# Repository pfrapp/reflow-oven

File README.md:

# reflow-oven
DIY reflow oven for SMD soldering

## Scope

In this project, we build an oven for reflow soldering of SMD (surface mount device)
parts, such as for instance microcontrollers etc.
In general, it will help to move away from THT (through hole technology)
boards and enter the realm of SMT (surface mount technology) boards.
This saves space, helps to get rid of evaluation-board-style setups,
and enables fully embedded circuits.
It basically makes the PCBs more professional and less tinker-ish.

This project is inspired by a reflow oven that I had at the university.
It was a predecessor of this one that you can currently buy at Beta Layout.
https://eu.beta-layout.com/estore/order_product_details.html?wg=1&p=740

Another inspiration is this instructable
https://www.instructables.com/DIY-REFLOW-OVEN/
that shows how to build a DIY oven.

The latter resource ends up with a self-contained oven, as the author wants
to be able to use it as a stand-alone tool.
It looks really professional and solid.

In this project, I just want to get the oven working in a first step.
Furthermore, I want to use the oven to build an improved version of the controller board
(kind of in a bootstrapping manner).
Also, the oven shall be usable and controllable from my computer.
For this reason, I will not disassemble the oven itself nor use an LCD
display, but just create an MVP which is a controller that
uses the actual oven as is.

## Idea

The general idea is to use an off-the-shelf pizza oven as the central
heating element or oven.
In the process of reflow soldering, we need to ensure that the temperature
follows a *reflow soldering profile*.

Therefore, we use a temperature probe to measure the temperature and
feed it back to a controller which generates the control signal.

This is a PWM signal,
as the temperature dynamics is very slow and hence acts as a natural
low-pass filter.
As the controller can only provide the signal, but not the actual power,
we use a solid-state relay (SSR) as the actuator
in order to transform the uC signal
to a mains voltage signal.

The controller algorithm runs on a Raspberry Pi. It is connected via
USB to a Cortex M4 microcontroller. The latter is used
to acquire the temperature signal and to create the PWM signal.

## Components

Here is an overview of the essential required components.

| Component                | Manufacturer      | Description                                            | Distributor   | Order no.       | Price (Euro)  |
|--------------------------|-------------------|--------------------------------------------------------|---------------|-----------------|---------------|
| SSR                      | Finder            | Steck-/Printrelais, 1x UM, 250V/10A, 5V, RM3,2         | Reichelt      | FIN 43.41.7 5V  | 5.95          |
| Temperatur probe         | UNI-T             | Temperaturfuehler, Typ K, universal                    | Reichelt      | UT TF-K         | 3.95          |
| Cortex M4 Eval Board     | TI                | TM4C1236 Evaluation Board with breakout pins           | DigiKey       | 2314937         | ca. 18        |
| Pizza oven               | Severin           | TO 2045 Oven, 1500 W, 100 to 230 deg C                 | Amazon        |                 | 60            |
| Fuse                     |                   | Feinsicherung 5x20mm, superflink (ff), 8A              | Reichelt      | ESKA 520.126    | ca. 2         |
| Fuse holder              |                   | 5 x 20 mm, 250 V, 10 A, black                          | Reichelt      | SCH 31010045    | 1.50          |
| Temperature converter    | Maxim Integrated  | MAX6675 (incl. cold junction compensation)             | Voelkner      | R025452         | ca. 7         |

### SSR

If there is no voltage applied at the input, then pins 11 and 12
(12 being the one close to A1 and A2) are connected.
Pins 11 and 14 are not connected.

The measured resistance between A1 and A2 is 97 Ohm for the 5V DC relay.

Hypothesis: If voltage is applied between A1 and A2 (use additional 22 Ohm resistor, transistor and impedance converter),
then pins 11 and 14 are connected.

This hypothesis is confirmed (using the lab supply):
Attaching 5 V via a 22 Ohm resistor to A1, and putting A2 on ground, makes pins 11 and 14 connected (no
resistance, connectivity test is positive).
Pins 11 and 12 are then disconnected.

Bei 5 V und 120 Ohm in Summe (97 vom Relais, 22 vom Vorwiderstand) erreichen wir den Bemessungsstrom von ca. 40 mA.
5000 mV / 120 Ohm = 42 mA.

Bei 12 V und 300 Ohm in Summe erhalten wir ebenfalls 12000 mV / 300 Ohm = 40 mA.
Die 300 Ohm setzen sich zusammen aus den 97 Ohm des Relais sowie aus 200 Ohm Vorwiderstand.
Dieser wiederum aus 150 Ohm sowie der Parallelschaltung einer Diode und ca. 100 Ohm.
Die Diode hat 100 Ohm, so dass diese Parallelschaltung 50 Ohm hat.
Die SMD Diode sollte, wie auch die bisherige THT Diode, 100 Ohm haben, da sie ca. 2.0 (THT 2.1) Volt
Forward Voltage bei 20 mA hat.
Parallelschaltung ist notwendig, damit der Bemessungsstrom von 40 mA erreicht wird, obwohl
die Diode nur 20 mA hat.

### Temperature probe

When the type K thermocouple is plugged into a volt meter,
one can see 0.0 mV.
This is because both the tip as well as the cold junction
are at the same temperature.

If the tip is heated by breathing at it, the voltage rises from 0.1 mV up to 0.3 mV.
When the tip is being put into an open oven that had a nominal temperature of 225 deg C,
the voltage rises to 2.0 mV or 2.1 mV.

Looking at the table from the second reference, this means that the temperature delta
is around 50 deg C (that is, ca. 70 deg C), which seems plausible given that the oven is open
and one can easily put the hand into it.

Resources
1. https://blog.beamex.com/de/thermoelement-kaltstellenkompensation-vergleichsstelle
2. https://www.omega.de/temperature/Z/pdf/z204-205iec.pdf

### Microcontroller

We use a Cortex M4 on a Tiva evaluation board.
It can be connected to the Raspberry Pi via USB.
The Raspberry Pi is connected to the host PC via Wi-Fi.

This allows
for the complete galvanic isolation between host PC
and reflow oven controller.

## Controller PCB

The controller board is a two-stage amplifier.
The signal from the microcontroller is first amplified using a BJT.
This signal is then used to control a relay.

Yet another stage is present on the Tiva board: It turned out that the
uC pins cannot reliably drive the BJT, so I introduced an impedance converter
using an OpAmp, see the following subsection.

### Impedance converter

Due to the switching of the relay, there are some voltage spikes on the transistor,
that is, on the low voltage side of the relay.

Those spikes are less pronounced when using the lab supply and more
pronounced when using the AD/DC converter.
They are there in any case though.

For this reason, an impedance converter or buffer is needed between the
uC pin and the controller board.

So far I tested the setup using this impedance converter and a lab supply
and it works.
In oder to test it without the lab supply I need a second AC/DC converter,
as the OpAmp needs a dual rail supply.

## Controller software

### Modelling of the reflow oven dynamics

The plant is modelled by a time delay followed by two first-order lag elements.

The parameters of the plant are identified by applying a step function
onto the oven. A 30% and 50% PWM signal is used for the step height.
Also, a 100% PWM step is applyied until a temperature of 100 deg C is reached.
In that case, also the cooling down is measured.

Here are some more details for the motivation of a first-order lag.
Note that we assume that there are two in order to model the
different behavior when heating and when cooling.
```
d_theta/dt = q_zu - q_ab

q_zu = K*u
q_ab = alpha*theta

K ... Proportional zur Leistung des Ofens
theta ... Abkuehlkoeffizient

d_theta/dt = K*u - alpha*theta

d_theta/dt + alpha*theta = K*u

s*Theta + alpha*Theta = K*U

(s + alpha) * Theta = K * U

G = Theta / U = K/(s + alpha)

```

Later a more complex model is used. You can find it in the Jupyter notebook.

### Control design

A PID controller is used for temperature control.
The parameters of a PI controller have been parameterized by the Ziegler-Nichols method.
Based on that, a PID controller has been manually tuned using the experimentally
identified plant.

## Tiva pin usage and connection

| Pin on Tiva   | Connected with                                  | Description        |
|---------------|------------------------------------------------:|-------------------:|
| GND           | Analog Thermo amplifier GND                     | Ground             |
| PE3           | Analog Thermo amplifier between 6.8k and 18k    | ADC input          |
| GND           | GND of BMP280 evaluation board                  | Ground             |
| +3.3V         | VCC of BMP280 evaluation board                  | Supply voltage     |
| PA6           | SCL of BMP280 evaluation board                  | I2C clock          |
| PA7           | SDA of BMP280 evaluation board                  | I2C data           |
| PB6           | Digital Thermo amplifier MISO                   | SPI data           |
| PB5           | Digital Thermo amplifier CS                     | SPI CS             |
| PB4           | Digital Thermo amplifier Clock                  | SPI clock          |
| PF4           | Controller board pin 2                          | Relay control      |

See also the following block diagram overview.

## General todos

- Add note to add LED signaling open thermocouple
- Add note to add LED signaling request to open door (manually)
- Add manual with important points, for instance
  - check for polarity of diodes and LEDs
  - Alignment of ICs

## Reference solder profiles

- https://www.7pcb.com/blog/lead-free-reflow-profile
- Data sheet of my solder paste
  https://de.beta-layout.com/elektronik-shop/loetzinn-lotpaste/10753-smd-lotpaste-iso-cream/
- TI application report
  **SPRABY1A MSL Ratings and Reflow Profiles** \
  https://www.ti.com/lit/an/spraby1a/spraby1a.pdf?ts=1741440364541

## Solder reports

### First SMD soldering with this setup (Oct-30, 2024)

- Lead-free HASL PCB (that is, no ENIG)
- No uC soldered (otherwise ENIG required)
- Stencil is required
- Soldered components: 0805 C, 0805 R (contain labels), Diodes, LEDs, OpAmps and other ICs
- Some parts on the PCB did not solder well --> longer preheat time, higher peak temperature, longer reflow time
- Fragmented setup was quite a mess --> higher integration of controller boards, fixture of the BMP280
- Power via lab supply --> Use TDK Lambdas in the future
- Timing of door opening to be made easier
- Application of solder paste --> not too much, also remove where there is too much before placing the part
- Add note to check for polarity of diodes and LEDs
- Reworking requires (no clean) flux

Time above 217 deg C: 52.5 seconds (with opening the door)<br />
Time between 150 and 180 deg C: 77.0 seconds<br />
Peak temperature: 237.0 deg C

### Second SMD soldering (Dec-23, 2024)

#### Compared with the first SMD soldering, I changed the following things:
- Adjusted solder temperature profile with the goal to allow for
  - more preheat time (goal reached)
  - higher peak temperature (not reached, peak temperature was actually slightly lower)
  - longer reflow time (goal reached)
- Better solder paste application
  - I made sure to apply the solder paste in a single round. That means,
    I ensured that I had enough of the paste on the upper edge
    of the stencil.
  - Then I went down slowly *once* while pressing firmly onto the stencil.
    It is important to not go back and forth (potentially allowing for too much solder paste).
  - The described procedure favors less solder paste being applied.
    As a consequence, I did not have to remove any surplus solder paste.
- I did *not* use a separate PCB to attach the thermocouple.
  Rather than that, I braided the thermocouple wire trough the grating of the grillage.
  I made sure that the tip was directly in between two grates, thus avoiding any contact
  of the termocouple tip with the metal grates (or with a dedicated PCB).
- I made the hint to open the door more prominent so that it could be
  seen when standing at the oven and looking on to the computer screen.
- I did solder a microcontroller. It was the 64-pin TM4C123GH6PM.
  Note that I ordered lead-free HASL (that is, the ENIG finish was not necessary).

#### Observations and facts
  - When opening the door, the thermocouple was detected as open, hence
    resulting in non-usable temperature measurements.
    As this was the cool-down phase anyway, no harm was induced.
  - I slipped while placing the Cortex onto the PCB.
    Apparently that was not a show-stopper.
    As can be seen on the magnified pictures I took, the solder paste
    had not been smeared away from the Cortex, but rather only between the pins.
  - The overall solder result was surprisingly good. I did not have to do any
    reworking and hence also did not need to use the no-clean flux.
  - It was raining, but I wanted to finish before Christmas, so I used an umbrella
    to protect the oven.

#### Open todos and fixes after this second soldering round
- USB Stencil checken (also ob Anmerkungen von jlcpcb umgesetzt wurden, erst in KiCad Lib, dann im Projekt)
- Highlight beim Bestuecken (z.B. eine PDF Seite pro Teil, erstellen via KiCad Python Script)
- Sanft positionieren (z.B. Halter fuer Pinzette konstruieren?)
- Dioden Polarity dokumentieren
- LEDs Polarity dokumentieren (fuer jede einzelne LED, da potentiell unterschiedlich pro Typ und zumindest unterschiedlich markiert)
  - Bei "Tetris" artigem Bild ist das kleine Quadrat die Kathode
  - Bei Dreieck ist die Spitze die Kathode
  - Auf der Vorderseite gibt es einen kleine gruene Markierung bei der Kathode
  - Auf dem Silk ist die geschlossene Seite die Kathode, die Anode ist offen
- LED Farben fixen im Schematic (2 mehr blue, 2 weniger gruen)
- Silk fuer Montage USB (also genaue Ausrichtung)
- Cortex Stencil checken (unterschiedlich grosse Luecken auf den Seiten)
  --> hat letztlich nichts gemacht
- SMD Bauteile einsortieren
- Inventur und nachbestellen, auch Resistors, Caps.
- Art Kreuze am Stencil fuer Ausrichtung (in allen 4 Ecken)
- Thermocouple open/closed sollte beides ueber LED direkt sichtbar sein
- Reflow Oven braucht einen Baking Modus (verschiedene Dauern und Temperaturen sollten auswaehlbar sein)
- Spannungsversorgung +12V/-12V auf einen Stecker packen, damit keine unipolare Spannungsversorgung moeglich ist (die mir schon mal den uC kaputt gemacht hat)
- Widerstand oder Zener auf PF4 Signal legen
```
(GPIO Output) --- [ 4.7 kΩ Resistor ] ---+--- (OpAmp Non-Inverting Input)
                                          |
                                    [ 3.3 V Zener Diode ]
                                          |
                                         GND
```

#### Output of the Jupyter script for solder profile analysis

Time above 217 deg C: 114.99984027777778 seconds (with opening the door)<br />
Time between 150 and 180 deg C: 91.99987222222222 seconds<br />
Peak temperature: 1023.75 deg C

Note that there was an error due to the thermocouple being open.
The values are rather<br />

Time above 217 deg C: 60 seconds (with opening the door)<br />
Time between 150 and 180 deg C: 91.99987222222222 seconds<br />
Peak temperature: 233 deg C

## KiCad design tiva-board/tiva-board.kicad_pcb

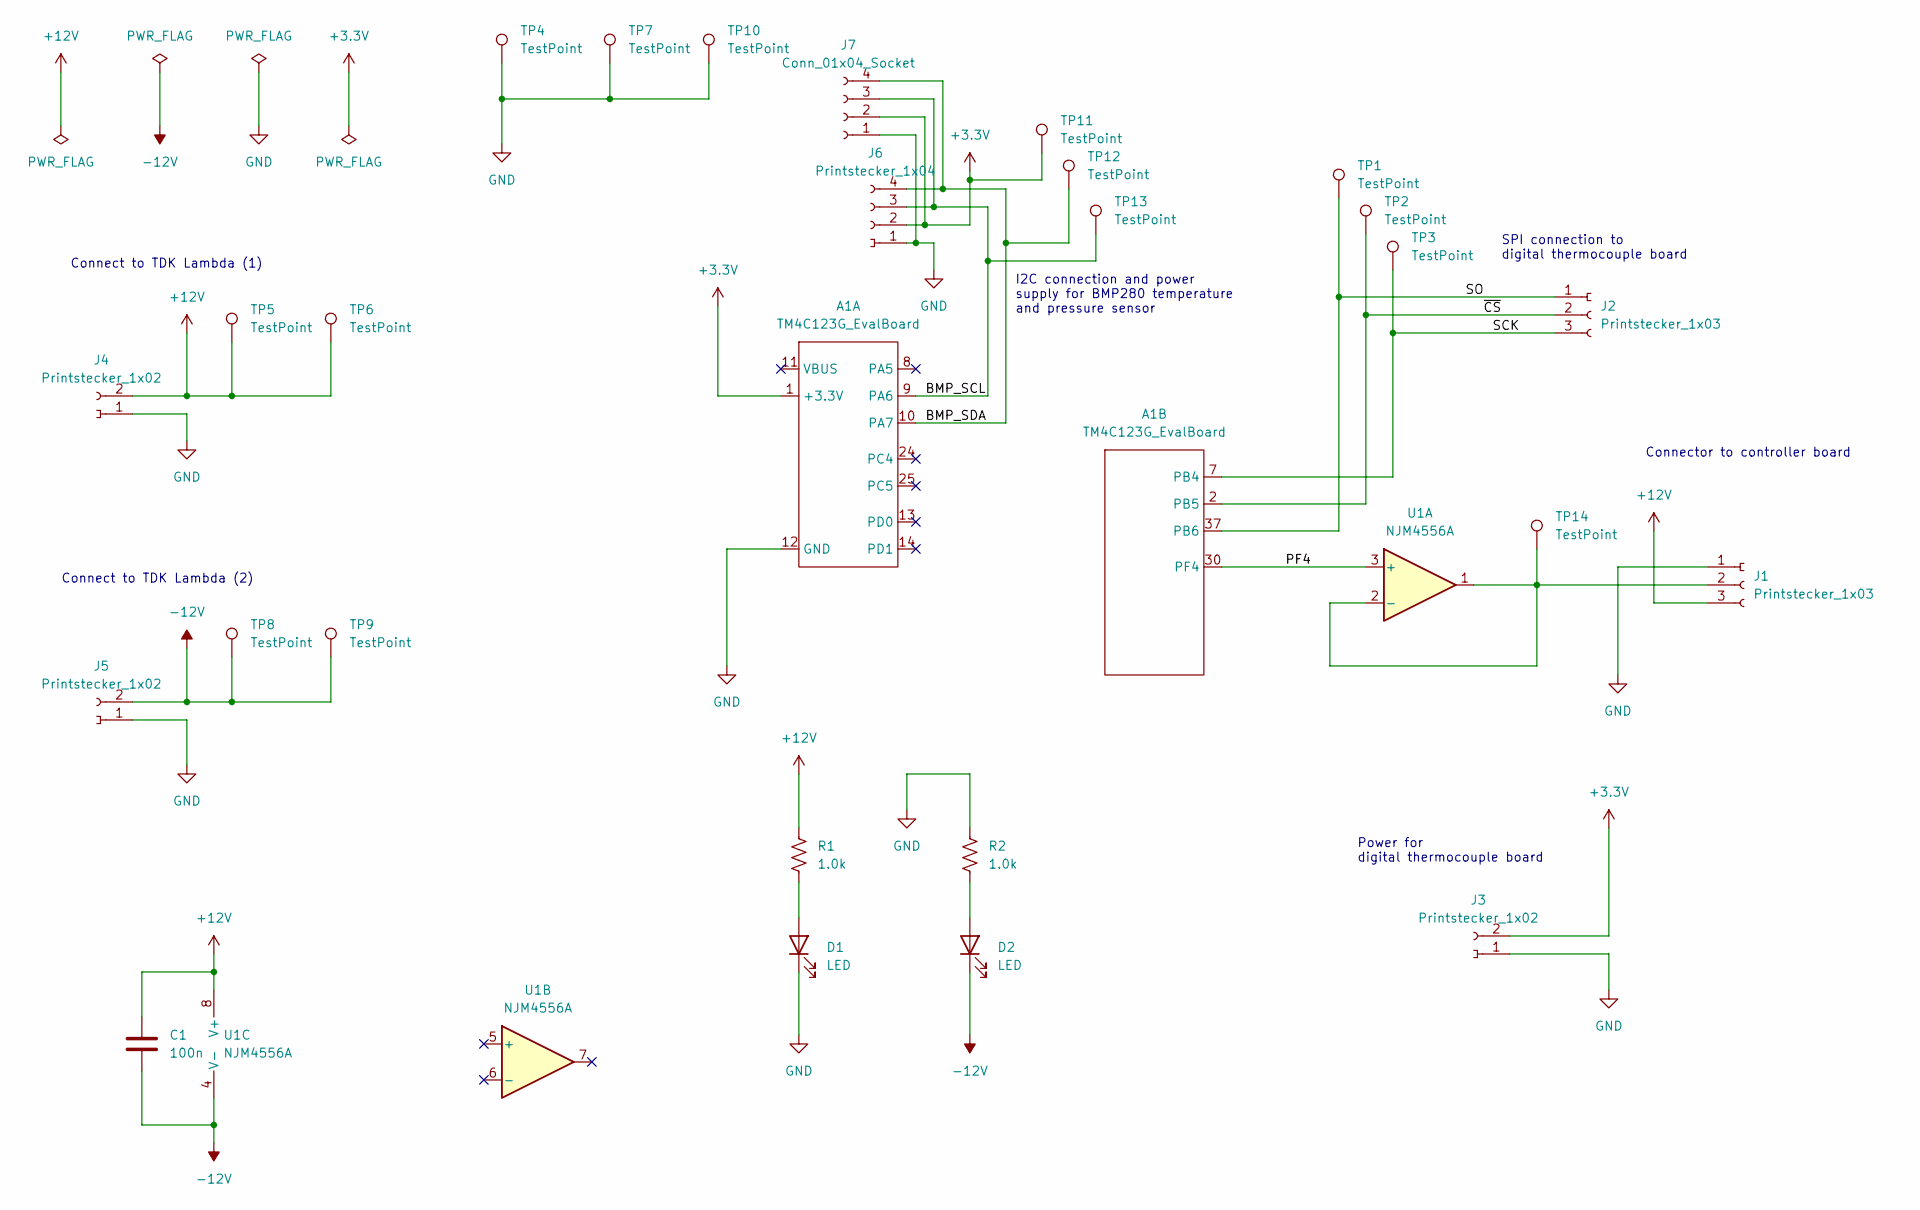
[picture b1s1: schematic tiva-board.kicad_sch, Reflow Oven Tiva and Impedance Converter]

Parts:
A1: TM4C123G_EvalBoard
C1: 100n; C_Disc_D5.0mm_W2.5mm_P2.50mm
D1, D2: LED; LED_D5.0mm
J1, J2: Printstecker_1x03; printstecker_1x03_P2.54mm
J3, J4, J5: Printstecker_1x02; printstecker_1x02_P2.54mm
J6: Printstecker_1x04; printstecker_1x04_P2.54mm
J7: Conn_01x04_Socket; PinSocket_1x04_P2.54mm_Vertical
R1, R2: 1.0k; R_Axial_DIN0207_L6.3mm_D2.5mm_P10.16mm_Horizontal
TP1, TP2, TP3, TP6, TP9, TP11, TP12, TP13, TP14: TestPoint; TestPoint_Pad_2.0x2.0mm
TP4, TP5, TP7, TP8, TP10: TestPoint; TestPoint_Plated_Hole_D2.0mm
U1: NJM4556A; DIP-8_W7.62mm

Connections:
+3.3V: A1.1 (+3.3V), J3.2, J6.2, J7.2, TP11.1
+12V: C1.1, J1.3, J4.2, R1.1, TP5.1, TP6.1, U1.8 (V+)
-12V: C1.2, D2.1 (K), J5.2, TP8.1, TP9.1, U1.4 (V-)
/BMP_SCL: A1.9 (PA6), J6.3, J7.3, TP13.1
/BMP_SDA: A1.10 (PA7), J6.4 (Pin_3), J7.4, TP12.1
/PF4: A1.30 (PF4), U1.3 (+)
/SCK: A1.7 (PB4), J2.3, TP3.1
/SO: A1.37 (PB6), J2.1, TP1.1
/~CS: A1.2 (PB5), J2.2, TP2.1
GND: A1.12 (GND), A1.31 (GND), D1.1 (K), J1.1, J3.1, J4.1, J5.1, J6.1, J7.1, R2.1, TP4.1, TP7.1, TP10.1
unnamed: D1.2 (A), R1.2
unnamed: D2.2 (A), R2.2
unnamed: J1.2, TP14.1, U1.1, U1.2 (-)

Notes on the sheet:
Power for digital thermocouple board
I2C connection and power supply for BMP280 temperature and pressure sensor
Connect to TDK Lambda (2)
Connect to TDK Lambda (1)
Connector to controller board
SPI connection to digital thermocouple board

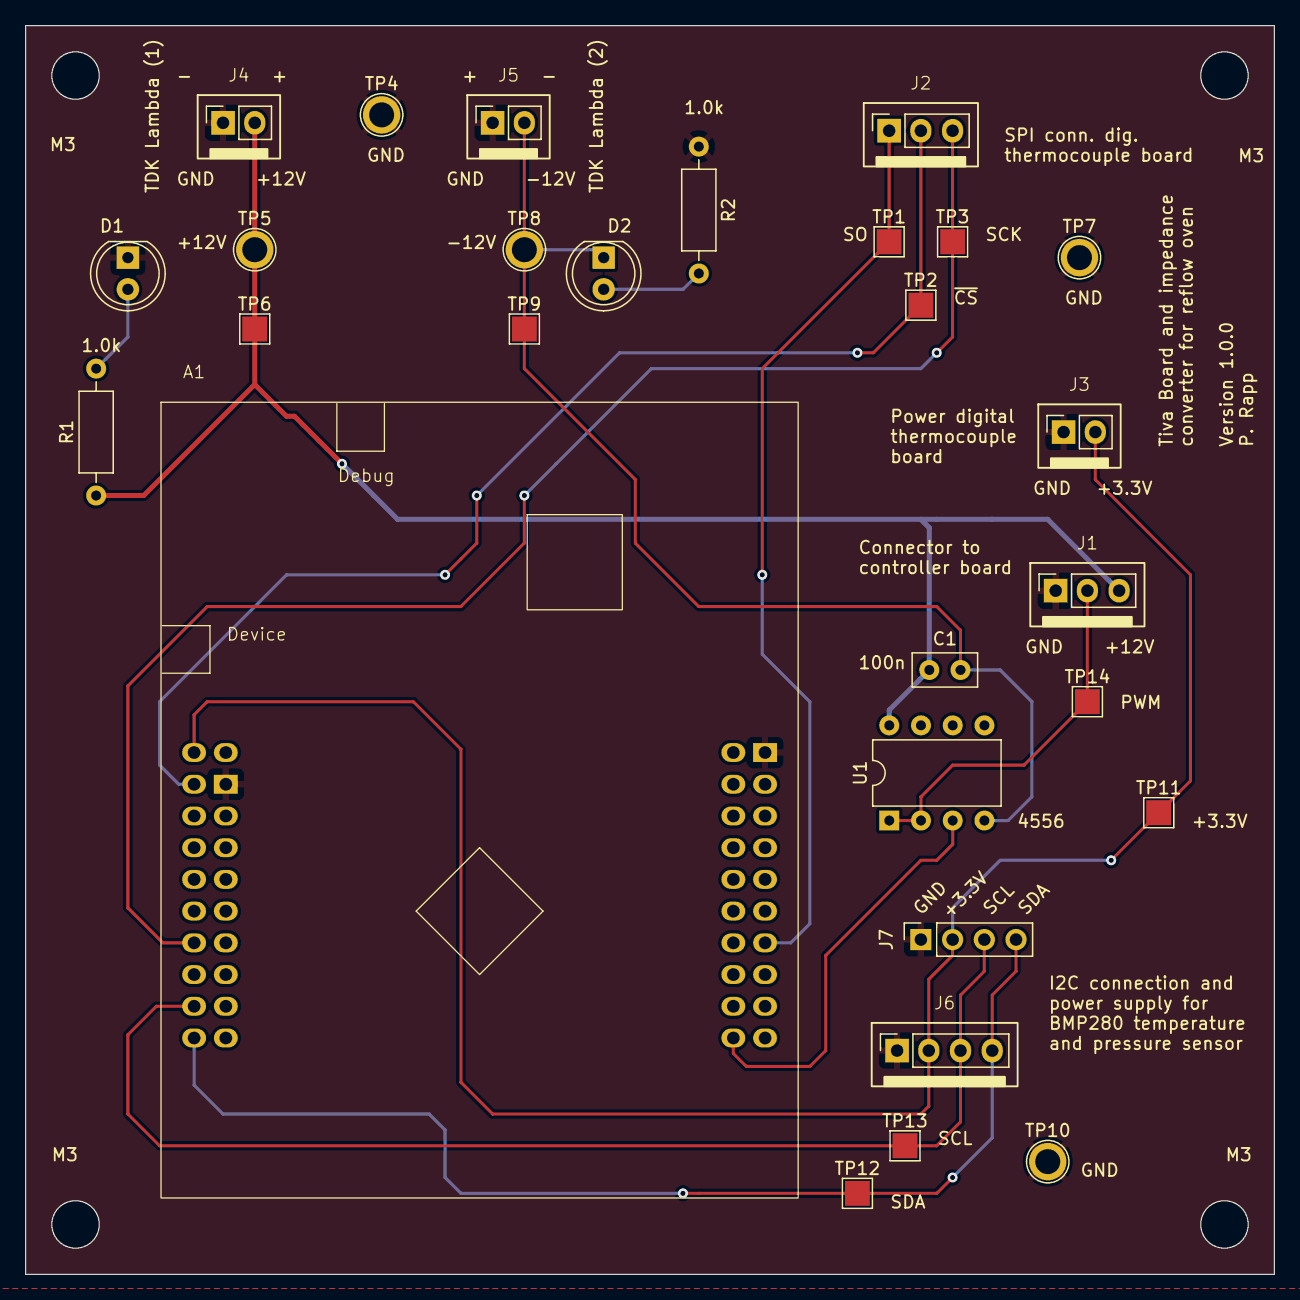
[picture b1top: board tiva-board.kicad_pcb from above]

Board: 2 copper layers, 100.0 x 100.0 mm, 28 parts (0 on the bottom side), 13 nets.

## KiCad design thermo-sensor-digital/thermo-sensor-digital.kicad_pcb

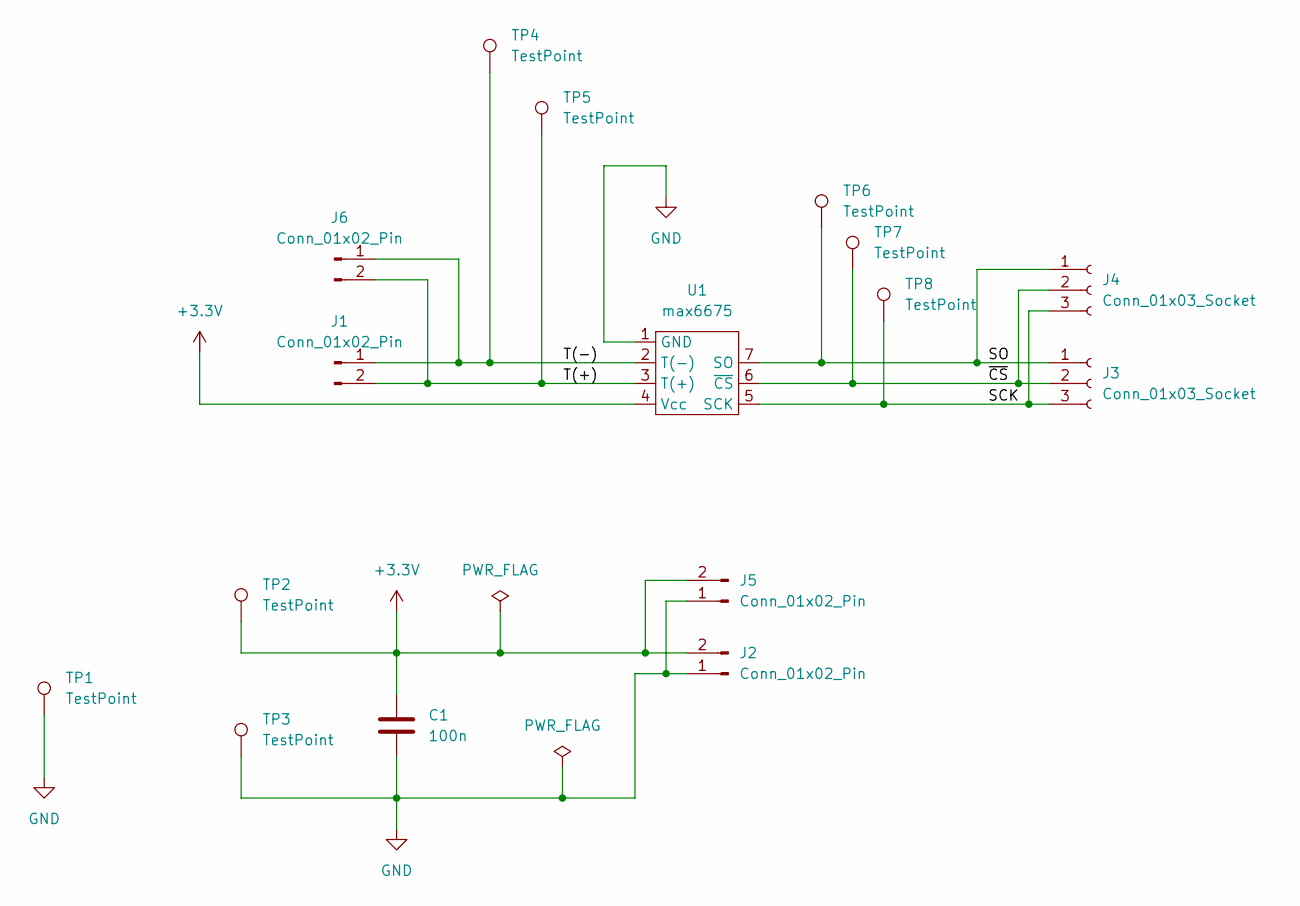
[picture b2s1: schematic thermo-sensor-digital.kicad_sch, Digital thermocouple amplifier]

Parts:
C1: 100n; C_Disc_D5.0mm_W2.5mm_P2.50mm
J1, J2, J5, J6: Conn_01x02_Pin; PinSocket_1x02_P2.54mm_Vertical
J3, J4: Conn_01x03_Socket; PinSocket_1x03_P2.54mm_Vertical
TP1: TestPoint; TestPoint_THTPad_4.0x4.0mm_Drill2.0mm
TP2, TP4, TP5, TP6, TP7, TP8: TestPoint; TestPoint_Pad_2.0x2.0mm
TP3: TestPoint; TestPoint_Plated_Hole_D2.0mm
U1: max6675

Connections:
+3.3V: C1.1, J2.2, J5.2, TP2.1, U1.4 (Vcc)
/SCK: J3.3, J4.3, TP8.1, U1.5 (SCK)
/SO: J3.1, J4.1, TP6.1, U1.7 (SO)
/T(+): J1.2, J6.2, TP5.1, U1.3 (T(+))
/T(-): J1.1, J6.1, TP4.1, U1.2 (T(-))
/~CS: J3.2, J4.2, TP7.1, U1.6 (~CS)
GND: C1.2, J2.1, J5.1, TP1.1, TP3.1, U1.1 (GND)

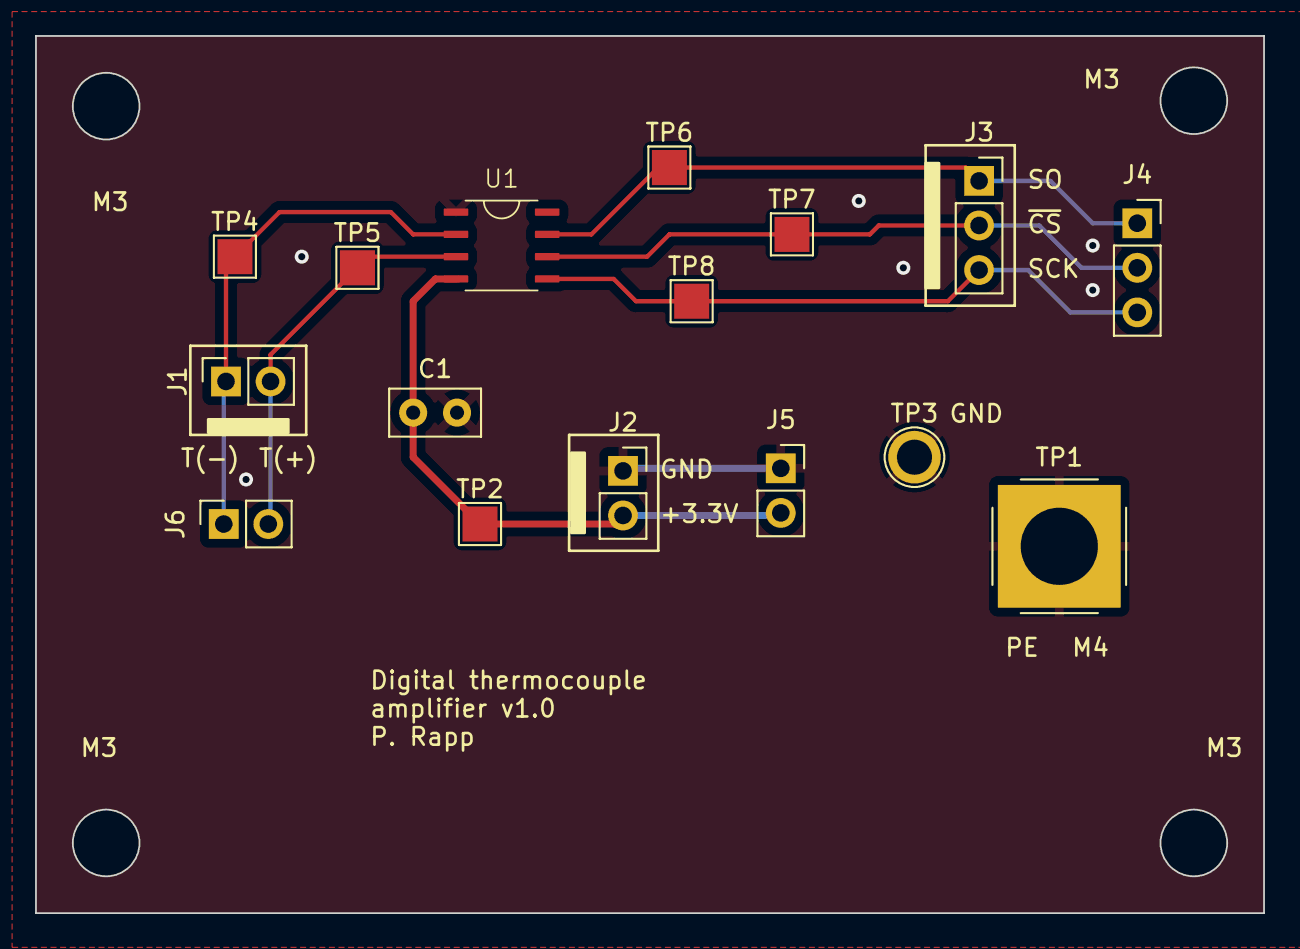
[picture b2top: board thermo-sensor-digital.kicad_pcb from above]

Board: 2 copper layers, 70.0 x 50.0 mm, 16 parts (0 on the bottom side), 7 nets.

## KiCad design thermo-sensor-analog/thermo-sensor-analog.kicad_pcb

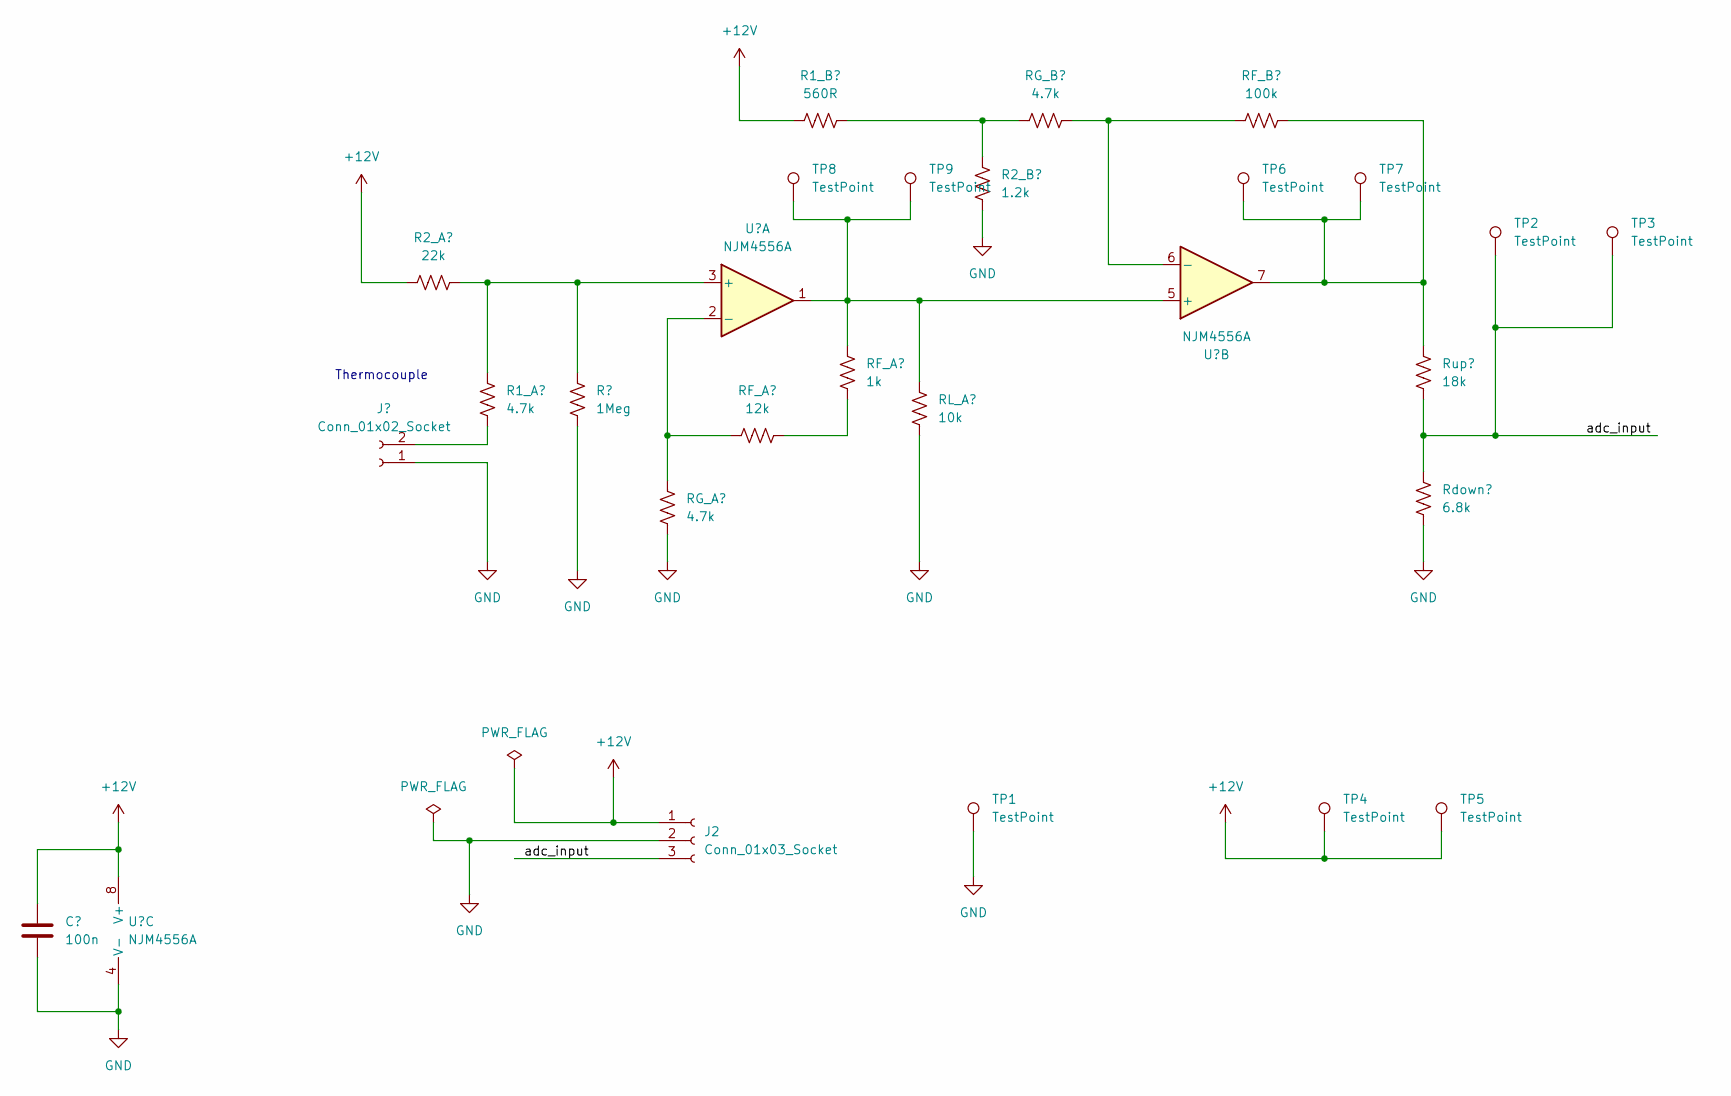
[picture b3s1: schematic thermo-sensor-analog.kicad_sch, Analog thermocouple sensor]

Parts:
C1: 100n; C_Disc_D5.0mm_W2.5mm_P2.50mm
J1: Conn_01x02_Socket; PinSocket_1x02_P2.54mm_Vertical
J2: Conn_01x03_Socket; PinSocket_1x03_P2.54mm_Vertical
R1: 22k; R_Axial_DIN0207_L6.3mm_D2.5mm_P10.16mm_Horizontal
R2, R4, R10: 4.7k; R_Axial_DIN0207_L6.3mm_D2.5mm_P10.16mm_Horizontal
R3: 1Meg; R_Axial_DIN0207_L6.3mm_D2.5mm_P10.16mm_Horizontal
R5: 12k; R_Axial_DIN0207_L6.3mm_D2.5mm_P10.16mm_Horizontal
R6: 560R; R_Axial_DIN0207_L6.3mm_D2.5mm_P10.16mm_Horizontal
R7: 1k; R_Axial_DIN0207_L6.3mm_D2.5mm_P10.16mm_Horizontal
R8: 10k; R_Axial_DIN0207_L6.3mm_D2.5mm_P10.16mm_Horizontal
R9: 1.2k; R_Axial_DIN0207_L6.3mm_D2.5mm_P10.16mm_Horizontal
R11: 100k; R_Axial_DIN0207_L6.3mm_D2.5mm_P10.16mm_Horizontal
R12: 18k; R_Axial_DIN0207_L6.3mm_D2.5mm_P10.16mm_Horizontal
R13: 6.8k; R_Axial_DIN0207_L6.3mm_D2.5mm_P10.16mm_Horizontal
TP1, TP2, TP4, TP6, TP8: TestPoint; TestPoint_Plated_Hole_D2.0mm
TP3, TP5, TP7, TP9: TestPoint; TestPoint_Pad_2.0x2.0mm
U1: NJM4556A; DIP-8_W7.62mm

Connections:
+12V: C1.1, J2.1, R1.1, R6.1, TP4.1, TP5.1, U1.8 (V+)
/adc_input: J2.3, R12.1, R13.2, TP2.1, TP3.1
GND: C1.2, J1.1, J2.2, R3.1, R4.1, R8.1, R9.1, R13.1, TP1.1, U1.4 (V-)
unnamed: J1.2, R2.1
unnamed: R5.2, R7.1
unnamed: R6.2, R9.2, R10.1
unnamed: R11.2, R12.2, TP6.1, TP7.1, U1.7
unnamed: R1.2, R2.2, R3.2, U1.3 (+)
unnamed: R4.2, R5.1, U1.2 (-)
unnamed: R7.2, R8.2, TP8.1, TP9.1, U1.1, U1.5 (+)
unnamed: R10.2, R11.1, U1.6 (-)

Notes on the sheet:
Thermocouple

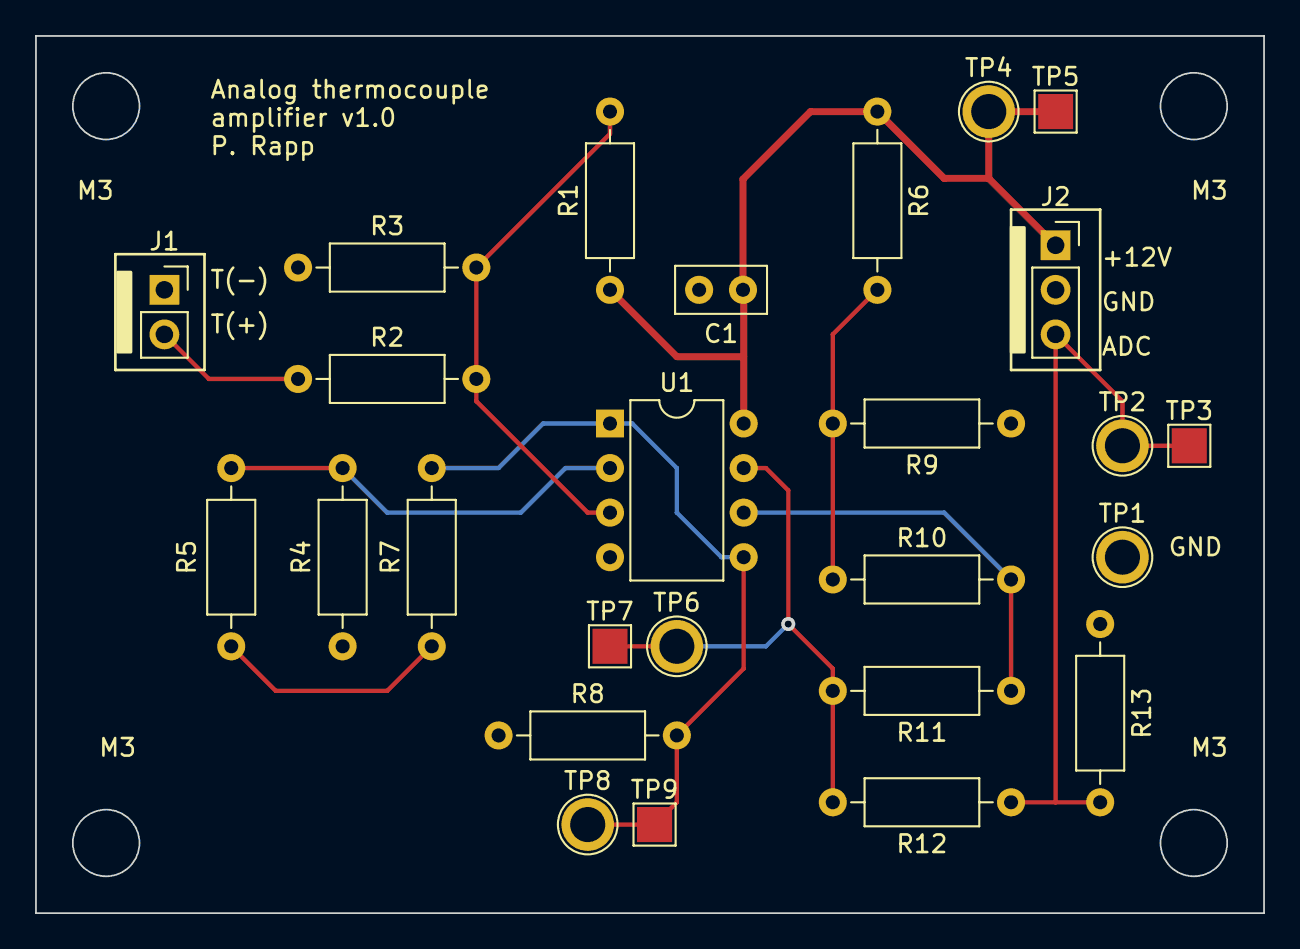
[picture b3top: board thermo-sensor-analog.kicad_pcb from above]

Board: 2 copper layers, 70.0 x 50.0 mm, 26 parts (0 on the bottom side), 11 nets.

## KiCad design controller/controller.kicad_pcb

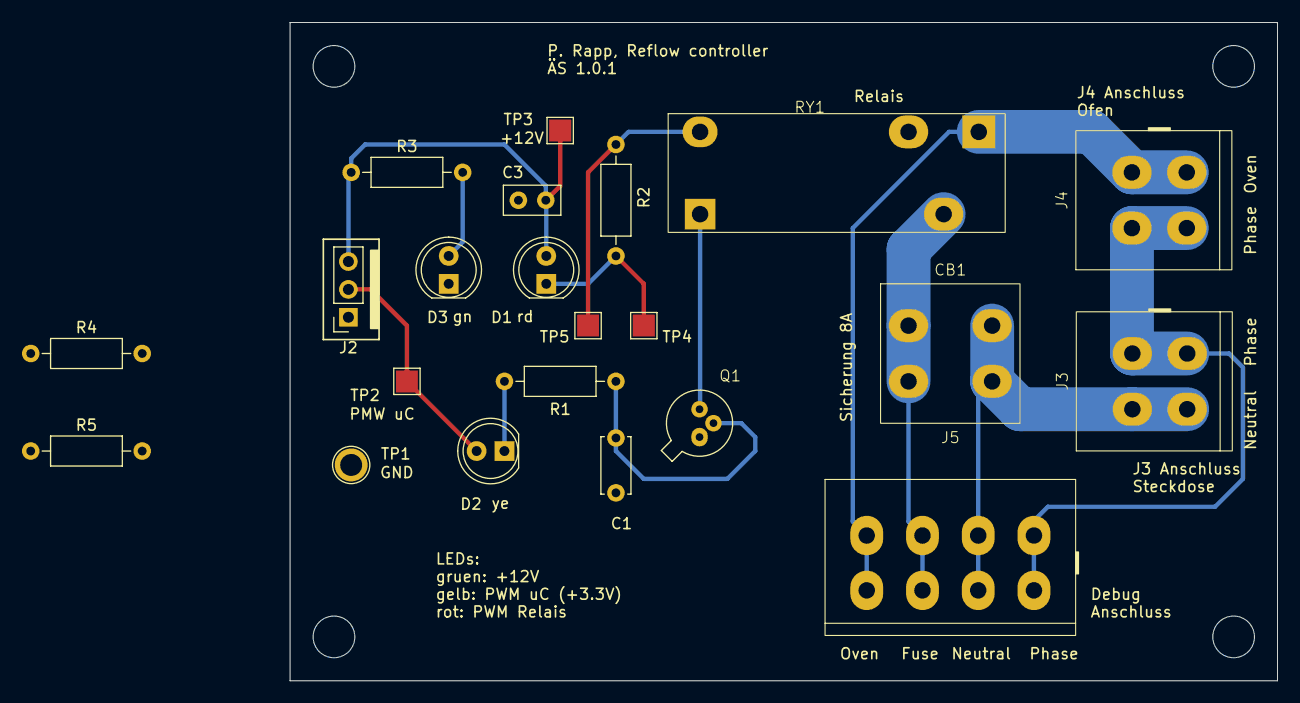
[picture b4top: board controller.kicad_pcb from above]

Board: 2 copper layers, 90.0 x 60.0 mm, 22 parts (0 on the bottom side), 14 nets.

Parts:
C1: 1n; C_Disc_D5.0mm_W2.5mm_P5.00mm
C3: 100n; C_Disc_D5.0mm_W2.5mm_P2.50mm
CB1: FPG4
D1: LED rd; LED_D5.0mm
D2: LED ye; LED_D5.0mm
D3: LED gn; LED_D5.0mm
J2: Conn_01x03_Socket; PinSocket_1x03_P2.54mm_Vertical
J3, J4: WAGO 236-402
J5: WAGO 236-404
Q1: 2N2222
R1: 100R; R_Axial_DIN0207_L6.3mm_D2.5mm_P10.16mm_Horizontal
R2: 150R; R_Axial_DIN0207_L6.3mm_D2.5mm_P10.16mm_Horizontal
R3: 3.9k; R_Axial_DIN0207_L6.3mm_D2.5mm_P10.16mm_Horizontal
R4, R5: 47R; R_Axial_DIN0207_L6.3mm_D2.5mm_P10.16mm_Horizontal
RY1: FIN_43.41.7; FIN 43.41.7
TP1: TestPoint; TestPoint_Plated_Hole_D2.0mm
TP2, TP3, TP4, TP5: TestPoint; TestPoint_Pad_2.0x2.0mm

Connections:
+12V: C3.1, D1.2 (A), J2.3, R3.1, R4.1, TP3.1
/Fuse: CB1.1 (A), CB1.2 (B), J5.3 (C), J5.4 (D), RY1.3 (11)
/Oven: J4.3 (C), J4.4 (D), J5.1 (A), J5.2 (B), RY1.5 (14)
AC: J3.3 (C), J3.4 (D), J4.1 (A), J4.2 (B), J5.7 (G), J5.8 (H)
Earth: CB1.3 (C), CB1.4 (D), J3.1 (A), J3.2 (B), J5.5 (E), J5.6 (F)
GND: C1.2, C3.2, D3.1 (K), J2.1, Q1.1 (E), TP1.1
unnamed: D1.1 (K), R2.1, R5.2, TP4.1
unnamed: D2.2 (A), J2.2, TP2.1
unnamed: D2.1 (K), R1.1
unnamed: D3.2 (A), R3.2
unnamed: C1.1, Q1.2 (B), R1.2
unnamed: Q1.3 (C), RY1.2 (A2)
unnamed: R4.2, R5.1
unnamed: R2.2, RY1.1 (A1), TP5.1

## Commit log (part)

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2024-01-22 Initial documentation
2024-01-28 Added a first version of the reflow controller
2024-02-04 Cleanup files; Add gitignore
2024-02-10 Added first box to hold the reflow controller PCB
2024-02-10 Added dimensions to board layout
2024-02-10 Updated ignored KiCad backup zip files
2024-02-10 Ignoring box stl and box fab files
2024-02-25 Documented defects of the first version of the reflow controller board
2024-03-03 Added measurement results for the controller board
2024-03-03 Added required changes for the printed box
2024-03-03 Incorporated changes to the reflow controller schematic (v1.0.0 to v1.0.1)
    Also incorporated some changes to the board, but did not place
    and route the two additional resistors.
2024-03-10 Added first test program for the reflow controller
2024-03-17 Removed more old backup files
2024-03-17 Read out the Who-Am-I register ot the BMP280 sensor
2024-03-23 Added host program to connect via USB
2024-03-23 Added USB on the Tiva
    Added USB code, includes, library, and interrupt handler.
2024-03-24 Changed measurement time and sampling frequency
2024-03-24 Restructured host code by using multiple source files
2024-03-24 Updated signals from tiva to host to carry
    The struct that carries the signals from the
    tiva to the host now contains the temperature
    and pressure measurement values as well as
    the trimming values.
2024-03-24 Enabled measurement on the sensor
2024-03-24 Read trimming values and evaluate physical temperature and pressure
    Include code from the sensor API in order to compute
    the physical values of the temperature and pressure.
2024-03-30 Removed old KiCad backups
2024-03-30 Fixed typo
2024-03-30 Added preliminary stage 3 for the amplifier
2024-03-30 Updated schematic
2024-03-30 Design of thermo couple amplifier
2024-03-30 Added computations for the resolution
2024-03-30 Designed simpler version of the thermo couple amplifier
2024-03-30 Updated values of thermo couple amplifier
2024-03-30 Added more references
2024-03-30 Changed voltage divider values to ensure 3.3V limit on Tiva
2024-03-30 Read out ADC0 on PE3 to get the amplified thermocouple voltage
2024-03-31 Log physical values and plot them in Python
    Replaced logging of the MSB and LSB by
    loggin of the physical values (as float or double).
    Created a script to read and plot the traces
    in Python.
2024-04-01 Updated signal plotting script
2024-04-01 Added analog thermo couple schematic and board
2024-04-03 Added digital thermo couple schematic and board
2024-04-06 Adde block diagram overview to readme
2024-05-19 Removed old backups
2024-05-22 Small refactoring
2024-05-22 Updated comments
2024-05-22 Added 20 mm more space for wires
2024-05-22 Increased height
2024-05-22 Added holes for mounting a cover
2024-05-23 Added holes to mount thermo couple banana plugs
2024-05-24 First attempt at reducing material
2024-05-25 Added dedicated structures to connect the mounting hole pattern
2024-05-25 Adjusted mounting holes for rail to fit M4
2024-05-26 Created lid for box
2024-07-15 Updated block diagram to accomodate the digital thermo amplifier
2024-07-15 Updated pin usage in readme
2024-07-15 Disable BMP280 and its I2C, enable SSI2 and read out MAX6675
2024-07-15 Extended description for BMP280
2024-07-16 Added info about two-stage amplifier design
2024-07-16 Updated section about microcontroller setup
2024-07-20 Send and use PWM signal for controller
2024-08-03 Fitted an exponential curve (PT1 with delay)
2024-08-03 Added the reference profile from the solder paste datasheet
2024-08-03 Designed PI controller via Ziegler-Nichols
2024-08-03 Extended the runtime from 120 s to 720 s
2024-08-03 Simulate the plant and test the PI controller in simulation
2024-08-03 Cleanup
2024-08-03 Fixed end time abort condition
2024-08-03 Removed LTspice files from gitignore
2024-08-03 Cleanup terminal output
2024-08-03 Fixed compile errors on Raspberry Pi
2024-08-03 Adapted Python script to read measurements
2024-08-03 Updated the reference and control signals
2024-08-03 Increased runtime from 10 to 120 seconds
2024-08-03 Explicitly set the GPIO PF4 as 8 mA output
    That did not help against the issues with
    the PWM not working correctly though
2024-08-03 Read reference and control signals from file
2024-08-03 Restructured simulation
2024-08-03 Added measurements for 30 and 50 percent PWM
2024-08-03 Introduced a dict for the PT1 with lag parameters
2024-08-03 Created step signal with Python
2024-08-03 Added screw mounting holes
2024-08-03 Introduced variables for length and width of the mount
2024-08-03 Adjusted dimensions
2024-08-03 Created the overall mount assembly view
2024-08-03 Started work on PCB mount
2024-08-03 Improved parameterization
2024-08-03 Added stencil mount
2024-08-03 Created PCB and stencil STLs for checking the assembly
2024-08-03 Renamed height variable
2024-08-03 Disable PWM if the temperature ever exceeded 100 deg C
2024-08-03 Increase control signal to 100 percent
2024-08-03 Moved the voltage spike description to the readme
2024-08-03 Restructured signal reading and plotting
2024-08-03 Fit model to 100 percent PWM with stop after 100 deg C have been reached
2024-08-04 Own PI controller design
2024-08-04 Changed control signal to be the PWM in percent
2024-08-10 Get intermediate signals (i.e., not only input and output) as well
2024-10-01 Added images to readme
2024-10-01 Extended documentation regarding the first-order lags
2024-10-03 Updated BOM
2024-10-03 Updated block diagram
2024-10-06 Created Gerber files for Tiva board
2024-10-06 Extended documentation on Tiva board
2024-10-19 Added mounting hole distance dimensions to PCB layout
2024-10-19 Created separate 3D part for the Tiva board
2024-11-10 Used structs instead of individual variables in logging
2024-11-10 Replaced PI by PID controller; Tuned controller on profile
2024-11-10 Clang-format the solder profile
2024-11-10 Perform system identification via optimization of the plant parameters
2024-11-10 Fixed controller and used parameters for it
2024-11-10 Implemented the controller in the host code
2024-11-10 Returned to original solder profile from the data sheet (without modifications)
2024-11-10 Added the plant simulation notebook
2024-11-10 Cleaned up and updated the signal reading python script
2024-11-10 Fixed percent sign escaping
2024-11-10 Performed final measurement before actually soldering the first time
2024-11-10 Added code to detect request to turn oven off (not yet implemented)
2024-11-10 Introduced and used dedicated time keeping struct
2024-11-10 Added reflow oven signals struct
2024-11-10 Emulate the simple system and test the subsystems
2024-11-10 Print out BMP280 temperature
2024-11-10 Add solder profile file; Add hint to open door
2024-11-10 Fixed clang-format file
2024-11-10 Open the door earlier to reduce time above liquidus line
2024-11-10 Enable usage of the BMP280 on Tiva again
2024-11-10 Removed unused file containing precomupted reference and control signals
2024-11-10 Add controlled measurements
2024-11-10 Implemented functionality to turn off oven directly (also disabled signal logging in that case)
2024-11-10 Get to know the Python control systems library better
2024-11-10 Clean up code; Preload measurements
2024-11-10 Updated clang-format file
2024-11-10 Added measurements (Oct. 27, 2024) of two steps (until 100 and 200 deg C) for system identification
2024-11-10 Removed unused variable
2024-11-10 Initialized and reworked controller parameter struct
2024-11-10 Use double values again
2024-11-10 Fix: inserted space
2024-11-10 Removed the unused logic that reads the reference signals from a file
2024-11-10 Moved controller structure to separate file
2024-11-10 Add general parameters to top of logfile
2024-11-10 Added and used system identification structure (parameters for manual testing)
2024-11-10 Added 2nd order system
2024-11-10 Performed first soldering task (wheel speed sensor); Adapted todos; Wrote short report
2024-11-10 Log the reference signal as well
2024-11-10 Fixed Heisenbug by initializing local variable before usage
2024-11-10 Fixed space
2024-11-10 Started with the controller design
2024-11-10 Change reference profile to allow larger heat peak; Evaluate controlled measurement
2024-11-10 Fixed parameters of (potentially) nonlinear system and disabled emulation of simple system
2024-11-10 Better runtime initialization
2024-11-10 Added struct for overall control parameters
2024-11-10 Added test and invalid operation modes; Enforced specification of operation mode
2024-11-10 Reduced delay and made it a parameter
2024-11-10 Added test profile for quick tests with short runtime and (almost) no heating up
2024-11-10 Partially replaced usage of controller struct by reflow oven signals struct
2024-11-10 Added interconnected system
2024-11-10 Put VS code settings folder on gitignore
2024-11-10 Updated resistor values on the Tiva board
2024-11-12 Added BMP280 mount
2024-11-14 Reworked BMP280 mount based on the first print
2024-11-14 Added comments about screw sizes
2024-11-15 Added DIN rail connector to Tiva board mount
2024-11-15 Import the BMP280 mount into the Tiva board mount
2024-12-08 Fixed date of first soldering in solder report
2024-12-08 Adapted soldering profile based on first run
    Based on the first PCB that I actually soldered
    with this oven on Oct-30, 2024, I adapted
    the soldering profile by increasing the
    preheat time and allowing for a longer
    peak time (in order to reach an actual
    higher peak temperature).
2024-12-08 Simplified values (evaluated addition)
2024-12-08 Adjusted profile again
    Adjusted the temperature profile again based on the
    measurement I just took:
    Increased preheat time, increased peak temperature.
    The latter mainly to make the controller go to
    max output.
2024-12-08 Made door opening hint more prominent
2024-12-08 Measurement of another profile adjustment
2024-12-17 Use pull-up on CS line
    Use a weak pull-up on the GPIO that is used
    as the chip select for the SPI.
    The idea was that the intermediate state of ca. 1 Volt
    does not occur.
    It did not occur that often, but is still present sometimes.
2024-12-17 Introduced waiting and toggling on CS
    Wait some time after the data on the SPI has been transferred.
    Also, toggle the chip select GPIO after the transmission
    (did not improve the bit shift errors).
    Also toggle it before.
    It seems that this did the trick and avoids the
    1 Volt state which in turn led to bit shift errors.
2024-12-17 Use push-pull instead of weak pull-up on CS
    Instead of the weak pull-up, use push-pull on the GPIO
    that is used for chip select.
    This did not solve the problem of the CS line
    going to 1 Volt sometimes though.
2024-12-21 Split plant simulation and measurement reading
    Created a separate Jupyter notebook for reading
    a measurement and removed measurement reading
    from the plant simulation Jupyter notebook.
2024-12-21 Final profile adjustement (incl. measurement) before 2nd solder
    This is the last and final adjustent of the solder profile
    before I try to solder the second PCB.
    This commit also contains the associated measurement.
2024-12-22 Added todo about door opening condition
2024-12-23 Added measurement of second soldered PCB
    This is the Cortex M4 board that I soldered on Dec 23, 2024.
    When opening the door to the oven, the thermocouple
    was open, so the temperature measurements are not correct.
    It was slightly raining on that day.
2025-03-09 Added another reflow profile (not to scale though)
2025-08-23 Put more STL files on gitignore
2025-08-23 Checking in measurement files
2025-08-23 Add more details about current computation
2025-08-23 Added the schematic of the thermo sensor and the MCU
    Not yet added the board itself.
    Also, the MCU needs to be replaced by the SMD part.
2025-08-24 Added missing schematics of hierarchical sheets
    I also connected T(-) to GND via a 0R resistor.
2025-08-24 Replaced symbols with custom print connector
